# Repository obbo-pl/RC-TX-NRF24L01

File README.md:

# RC-TX-NRF24L01
2.4GHz module for Sanwa VG6DR based on NRF24L01 G-24 working with standard firmware https://github.com/pascallanger/DIY-Multiprotocol-TX-Module

For more information: [www.obbo.pl](https://www.obbo.pl/sanwa_vg6)

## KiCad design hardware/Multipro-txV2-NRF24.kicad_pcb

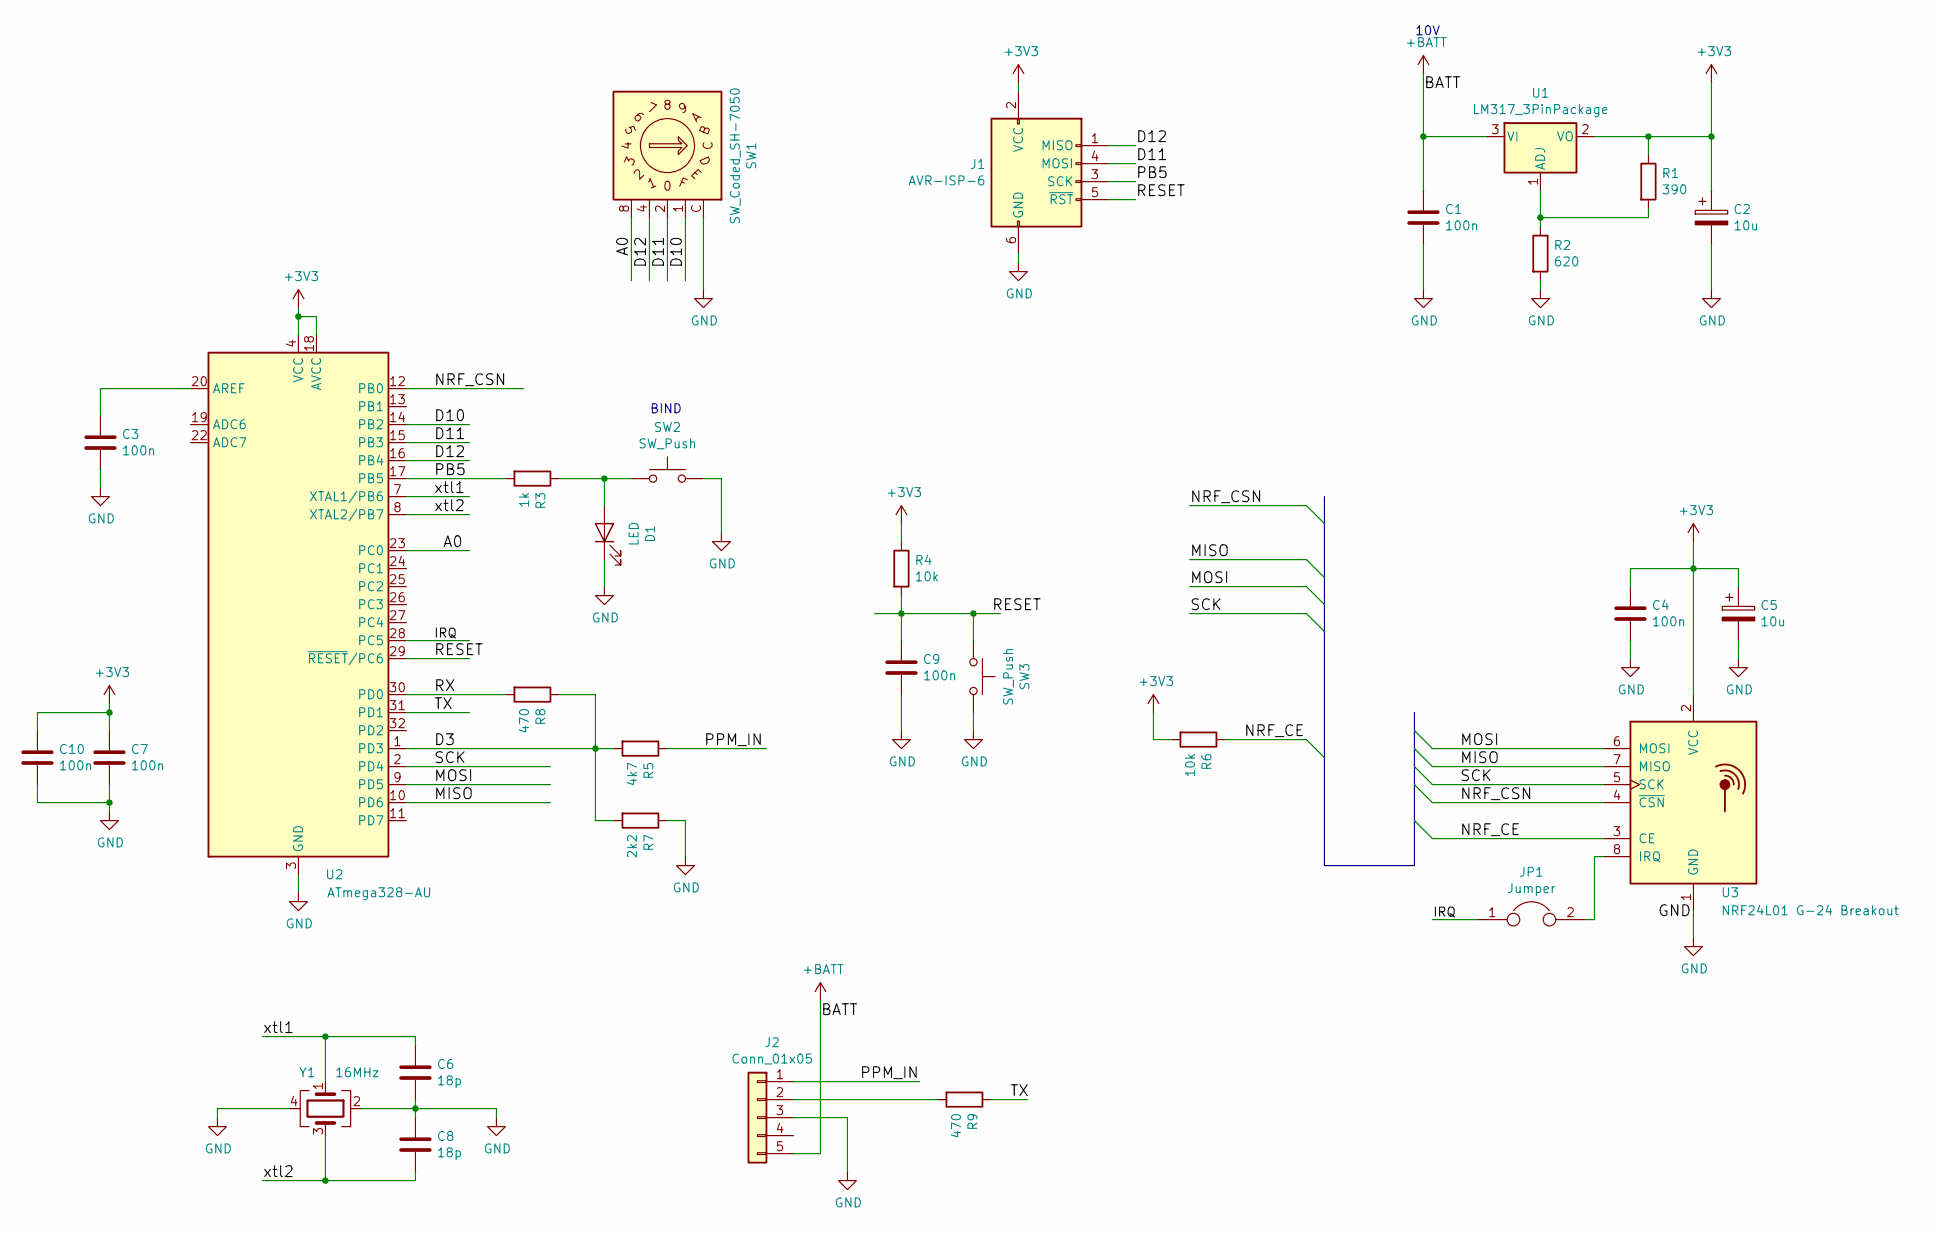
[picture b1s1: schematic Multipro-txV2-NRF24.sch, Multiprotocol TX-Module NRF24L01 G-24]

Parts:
C1, C3, C4, C7, C9, C10: 100n; C_0805K
C2, C5: 10u; C_1210_3225Metric_Pad1.42x2.65mm_HandSolder
C6, C8: 18p; C_0805K
D1: LED; LED_0805_2012Metric_Pad1.15x1.40mm_HandSolder
J1: AVR-ISP-6; PinHeader_2x03_P2.54mm_Horizontal
J2: Conn_01x05; PinHeader_1x05_P2.54mm_Vertical
JP1: Jumper; R_0805K
R1: 390; R_0805K
R2: 620; R_0805K
R3: 1k; R_0805K
R4, R6: 10k; R_0805K
R5: 4k7; R_0805K
R7: 2k2; R_0805K
R8, R9: 470; R_0805K
SW1: SW_Coded_SH-7050; Rotary_switch_coded_7x7_SMD
SW2, SW3: SW_Push; SW_SPST_PTS645
U1: LM317_3PinPackage; TO-252-2-DPAK
U2: ATmega328-AU; TQFP-32_7x7mm_P0.8mm
U3: NRF24L01 G-24 Breakout; nRF24L01-GT24_Breakout
Y1: 16MHz; Crystal_SMD_5032-4Pin_5.0x3.2mm_HandSoldering

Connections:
+3V3: C2.1, C4.1, C5.1, C7.1, C10.1, J1.2 (VCC), R1.1, R4.1, R6.2, U1.2 (VO), U2.4 (VCC), U2.6 (VCC), U2.18 (AVCC), U3.2 (VCC)
+BATT: C1.1, J2.5, U1.3 (VI)
/A0: SW1.8, U2.23 (PC0)
/D3: R5.2, R7.2, R8.1, U2.1 (PD3)
/D10: SW1.1, U2.14 (PB2)
/D11: J1.4 (MOSI), SW1.2, U2.15 (PB3)
/D12: J1.1 (MISO), SW1.4, U2.16 (PB4)
/IRQ: JP1.1, U2.28 (PC5)
/MISO: U2.10 (PD6), U3.7 (MISO)
/MOSI: U2.9 (PD5), U3.6 (MOSI)
/NRF_CE: R6.1, U3.3 (CE)
/NRF_CSN: U2.12 (PB0), U3.4 (~CSN)
/PB5: J1.3 (SCK), R3.2, U2.17 (PB5)
/PPM_IN: J2.1, R5.1
/RESET: C9.1, J1.5 (~RST), R4.2, SW3.1, U2.29 (~RESET~/PC6)
/RX: R8.2, U2.30 (PD0)
/SCK: U2.2 (PD4), U3.5 (SCK)
/TX: R9.1, U2.31 (PD1)
/xtl1: C6.1, U2.7 (XTAL1/PB6), Y1.1
/xtl2: C8.2, U2.8 (XTAL2/PB7), Y1.3
GND: C1.2, C2.2, C3.2, C4.2, C5.2, C6.2, C7.2, C8.1, C9.2, C10.2, D1.1 (K), J1.6 (GND), J2.3, R2.2, R7.1, SW1.C, SW2.2, SW3.2, U2.3 (GND), U2.5 (GND), U2.21 (GND), U3.1 (GND), Y1.2, Y1.4
unnamed: C3.1, U2.20 (AREF)
unnamed: D1.2 (A), R3.1, SW2.1
unnamed: J2.2, R9.2
unnamed: JP1.2, U3.8 (IRQ)
unnamed: R1.2, R2.1, U1.1 (ADJ)

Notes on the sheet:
BIND
10V

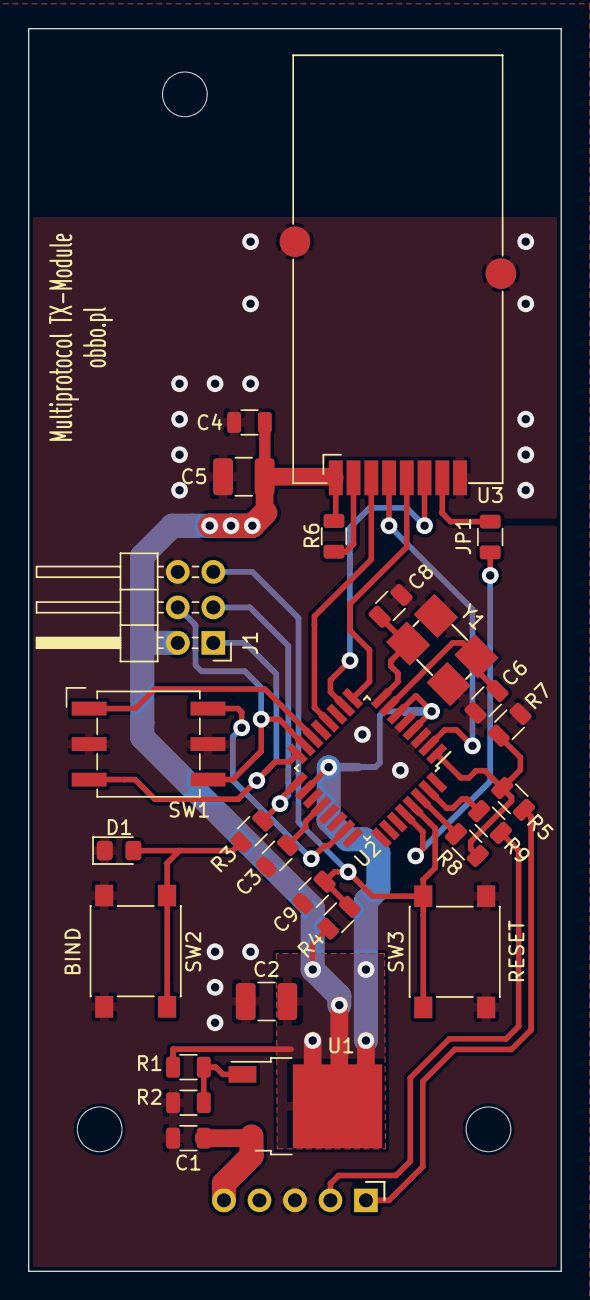
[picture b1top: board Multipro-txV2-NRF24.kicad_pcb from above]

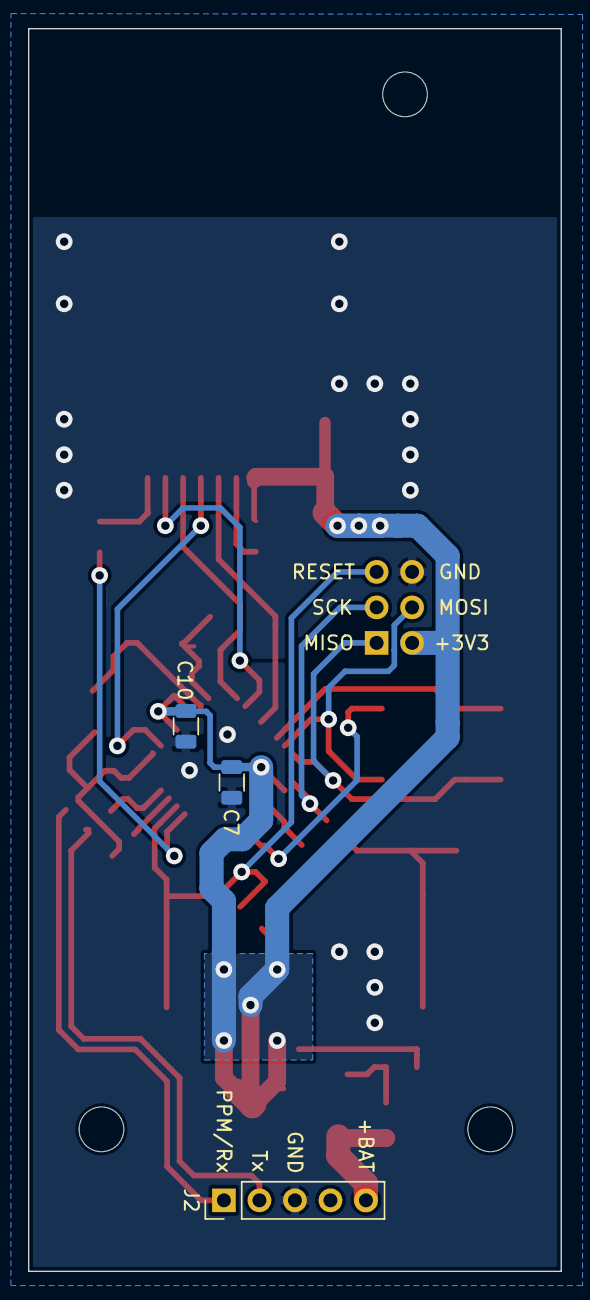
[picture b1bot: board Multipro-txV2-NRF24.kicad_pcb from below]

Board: 2 copper layers, 38.1 x 88.9 mm, 30 parts (3 on the bottom side), 26 nets.

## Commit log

2020-08-28 values update
2020-08-28 added delay for correct checking of "BIND" button state
